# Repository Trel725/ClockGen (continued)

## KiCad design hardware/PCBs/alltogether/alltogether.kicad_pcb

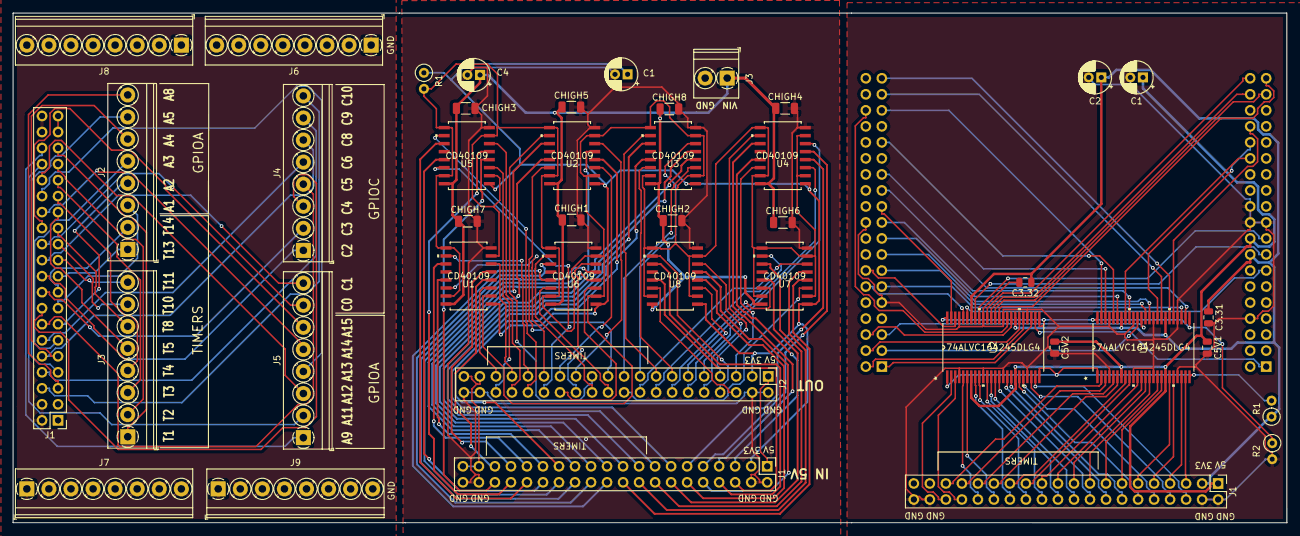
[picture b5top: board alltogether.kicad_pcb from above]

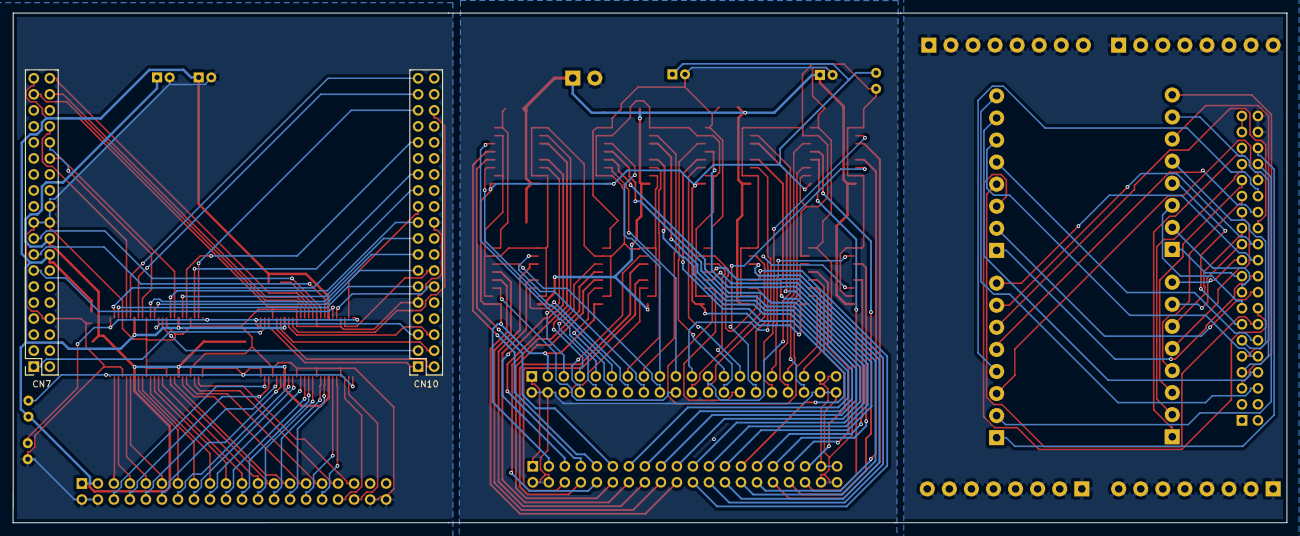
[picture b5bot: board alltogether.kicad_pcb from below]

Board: 2 copper layers, 202.0 x 80.8 mm, 44 parts (2 on the bottom side), 105 nets.

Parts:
C1, C1#2, C2, C4: CP; CP_Radial_D5.0mm_P2.00mm
C3.31, C3.32, C5V1, C5V2: C; C_0805_2012Metric
CHIGH1, CHIGH2, CHIGH3, CHIGH4, CHIGH5, CHIGH6, CHIGH7, CHIGH8: C; C_1206_3216Metric
CN7, CN10: Conn_02x19_Odd_Even; PinSocket_2x19_P2.54mm_Vertical
J1, J1#2, J1#3, J2#2: Conn_02x20_Odd_Even; PinHeader_2x20_P2.54mm_Vertical
J2, J3, J4, J5, J6, J7, J8, J9: Screw_Terminal_01x08; TerminalBlock_Phoenix_PT-1,5-8-3.5-H_1x08_P3.50mm_Horizontal
J3#2: Conn_01x02_Female; TerminalBlock_Phoenix_PT-1,5-2-3.5-H_1x02_P3.50mm_Horizontal
R1: 1K; R_Axial_DIN0207_L6.3mm_D2.5mm_P2.54mm_Vertical
R1#2, R2: 10K; R_Axial_DIN0207_L6.3mm_D2.5mm_P2.54mm_Vertical
U1, U2, U3, U4, U5, U6, U7, U8: CD40109; CD40109BNSR
U1#2, U2#2: 74ALVC164245DLG4

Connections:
+3V3: C1.1, C2.1, C3.31.1, C3.32.1, CN7.16, J1#2.3, J1#3.3, J2#2.3, R1.1, R1#2.1, U1.1, U1#2.31, U1#2.42, U2.1, U2#2.31, U2#2.42, U3.1, U4.1, U5.1, U6.1, U7.1, U8.1
+5V: C1#2.1, C5V1.1, C5V2.1, CN7.18, J1#3.1, U1#2.7, U1#2.18, U2#2.7, U2#2.18
+15V: C4.1, CHIGH1.1, CHIGH2.1, CHIGH3.1, CHIGH4.1, CHIGH5.1, CHIGH6.1, CHIGH7.1, CHIGH8.1, J3#2.1, U1.16, U2.16, U3.16, U4.16, U5.16, U6.16, U7.16, U8.16
/+5V: J1#2.1, J2#2.1
/NC: J1.37, J1.39, J1#2.37, J1#2.39, J2#2.37, J2#2.39
/PA0: CN7.28, U1#2.41
/PA0_5V: J1.27, J1#3.27, J2#2.27, J3.5, U1#2.8, U2.3
/PA0_HIGH: J1#2.27, U2.4
/PA1: CN7.30, U1#2.33
/PA1_5V: J1.15, J1#3.15, J2.3, J2#2.15, U1#2.16, U3.10
/PA1_HIGH: J1#2.15, U3.11
/PA2: CN10.35, U1#2.32
/PA2_5V: J1.13, J1#3.13, J2.4, J2#2.13, U1#2.17, U3.14
/PA2_HIGH: J1#2.13, U3.13
/PA3: CN10.37, U1#2.30
/PA3_5V: J1.11, J1#3.11, J2.5, J2#2.11, U1#2.19, U4.3
/PA3_HIGH: J1#2.11, U4.4
/PA4: CN7.32, U1#2.29
/PA4_5V: J1.9, J1#3.9, J2.6, J2#2.9, U1#2.20, U4.6
/PA4_HIGH: J1#2.9, U4.5
/PA5: CN10.11, U1#2.27
/PA5_5V: J1.7, J1#3.7, J2.7, J2#2.7, U1#2.22, U4.10
/PA5_HIGH: J1#2.7, U4.11
/PA6: CN10.13, U1#2.36
/PA6_5V: J1.19, J1#3.19, J2.1, J2#2.19, U1#2.13, U3.3
/PA6_HIGH: J1#2.19, U3.4
/PA7: CN10.15, U1#2.35
/PA7_5V: J1.17, J1#3.17, J2.2, J2#2.17, U1#2.14, U3.6
/PA7_HIGH: J1#2.17, U3.5
/PA8: CN10.23, U1#2.26
/PA8_5V: J1.5, J1#3.5, J2.8, J2#2.5, U1#2.23, U4.14
/PA8_HIGH: J1#2.5, U4.13
/PA9: CN10.21, U2#2.47
/PA9_5V: J1.36, J1#3.36, J2#2.36, J5.1, U2#2.2, U5.3
/PA9_HIGH: J1#2.36, U5.4
/PA10: CN10.33, U1#2.47
/PA10_5V: J1.35, J1#3.35, J2#2.35, J3.1, U1.3, U1#2.2
/PA10_HIGH: J1#2.35, U1.4
/PA11: CN10.14, U2#2.46
/PA11_5V: J1.34, J1#3.34, J2#2.34, J5.2, U2#2.3, U5.6
/PA11_HIGH: J1#2.34, U5.5
/PA12: CN10.12, U2#2.44
/PA12_5V: J1.32, J1#3.32, J2#2.32, J5.3, U2#2.5, U5.10
/PA12_HIGH: J1#2.32, U5.11
/PA13: CN7.13, U2#2.43
/PA13_5V: J1.30, J1#3.30, J2#2.30, J5.4, U2#2.6, U5.14
/PA13_HIGH: J1#2.30, U5.13
/PA14: CN7.15, U2#2.41
/PA14_5V: J1.28, J1#3.28, J2#2.28, J5.5, U2#2.8, U6.3
/PA14_HIGH: J1#2.28, U6.4
/PA15: CN7.17, U2#2.40
/PA15_5V: J1.26, J1#3.26, J2#2.26, J5.6, U2#2.9, U6.6
/PA15_HIGH: J1#2.26, U6.5
/PB5: CN10.29, U1#2.44
/PB5_5V: J1.31, J1#3.31, J2#2.31, J3.3, U1.10, U1#2.5
/PB5_HIGH: J1#2.31, U1.11
/PB6: CN10.17, U1#2.43
/PB6_5V: J1.29, J1#3.29, J2#2.29, J3.4, U1.14, U1#2.6
/PB6_HIGH: J1#2.29, U1.13
/PB8: CN10.3, U1#2.38
/PB8_5V: J1.23, J1#3.23, J2#2.23, J3.7, U1#2.11, U2.10
/PB8_HIGH: J1#2.23, U2.11
/PB9: CN10.5, U1#2.37
/PB9_5V: J1.21, J1#3.21, J2#2.21, J3.8, U1#2.12, U2.14
/PB9_HIGH: J1#2.21, U2.13
/PB10: CN10.25, U1#2.46
/PB10_5V: J1.33, J1#3.33, J2#2.33, J3.2, U1.6, U1#2.3
/PB10_HIGH: J1#2.33, U1.5
/PC0: CN7.38, U2#2.38
/PC0_5V: J1.24, J1#3.24, J2#2.24, J5.7, U2#2.11, U6.10
/PC0_HIGH: J1#2.24, U6.11
/PC1: CN7.36, U2#2.37
/PC1_5V: J1.22, J1#3.22, J2#2.22, J5.8, U2#2.12, U6.14
/PC1_HIGH: J1#2.22, U6.13
/PC2: CN7.35, U2#2.36
/PC2_5V: J1.20, J1#3.20, J2#2.20, J4.1, U2#2.13, U7.3
/PC2_HIGH: J1#2.20, U7.4
/PC3: CN7.37, U2#2.35
/PC3_5V: J1.18, J1#3.18, J2#2.18, J4.2, U2#2.14, U7.6
/PC3_HIGH: J1#2.18, U7.5
/PC4: CN10.34, U2#2.33
/PC4_5V: J1.16, J1#3.16, J2#2.16, J4.3, U2#2.16, U7.10
/PC4_HIGH: J1#2.16, U7.11
/PC5: CN10.6, U2#2.32
/PC5_5V: J1.14, J1#3.14, J2#2.14, J4.4, U2#2.17, U7.14
/PC5_HIGH: J1#2.14, U7.13
/PC6: CN10.4, U2#2.30
/PC6_5V: J1.12, J1#3.12, J2#2.12, J4.5, U2#2.19, U8.3
/PC6_HIGH: J1#2.12, U8.4
/PC7: CN10.19, U1#2.40
/PC7_5V: J1.25, J1#3.25, J2#2.25, J3.6, U1#2.9, U2.6
/PC7_HIGH: J1#2.25, U2.5
/PC8: CN10.2, U2#2.29
/PC8_5V: J1.10, J1#3.10, J2#2.10, J4.6, U2#2.20, U8.6
/PC8_HIGH: J1#2.10, U8.5
/PC9: CN10.1, U2#2.27
/PC9_5V: J1.8, J1#3.8, J2#2.8, J4.7, U2#2.22, U8.10
/PC9_HIGH: J1#2.8, U8.11
/PC10: CN7.1, U2#2.26
/PC10_5V: J1.6, J1#3.6, J2#2.6, J4.8, U2#2.23, U8.14
/PC10_HIGH: J1#2.6, U8.13
/PULLDOWN: R2.1, U1#2.25, U1#2.48, U2#2.25, U2#2.48
/PULLUP: R1#2.2, U1#2.1, U1#2.24, U2#2.1, U2#2.24
/PULLUP_HIGH: R1.2, U1.2, U1.7, U1.9, U1.15, U2.2, U2.7, U2.9, U2.15, U3.2, U3.7, U3.9, U3.15, U4.2, U4.7, U4.9, U4.15, U5.2, U5.7, U5.9, U5.15, U6.2, U6.7, U6.9, U6.15, U7.2, U7.7, U7.9, U7.15, U8.2, U8.7, U8.9, U8.15
GND: C1.2, C1#2.2, C2.2, C3.31.2, C3.32.2, C4.2, C5V1.2, C5V2.2, CHIGH1.2, CHIGH2.2, CHIGH3.2, CHIGH4.2, CHIGH5.2, CHIGH6.2, CHIGH7.2, CHIGH8.2, CN7.8, CN7.19, CN7.20, CN7.22, CN10.9, CN10.20, J1.2, J1.4, J1.38, J1.40, J1#2.2, J1#2.4, J1#2.38, J1#2.40, J1#3.2, J1#3.4, J1#3.38, J1#3.40, J2#2.2, J2#2.4, J2#2.38, J2#2.40, J3#2.2, J6.1, J6.2, J6.3, J6.4, J6.5, J6.6, J6.7, J6.8, J7.1, J7.2, J7.3, J7.4, J7.5, J7.6, J7.7, J7.8, J8.1, J8.2, J8.3, J8.4, J8.5, J8.6, J8.7, J8.8, J9.1, J9.2, J9.3, J9.4, J9.5, J9.6, J9.7, J9.8, R2.2, U1.8, U1#2.4, U1#2.10, U1#2.15, U1#2.21, U1#2.28, U1#2.34, U1#2.39, U1#2.45, U2.8, U2#2.4, U2#2.10, U2#2.15, U2#2.21, U2#2.28, U2#2.34, U2#2.39, U2#2.45, U3.8, U4.8, U5.8, U6.8, U7.8, U8.8

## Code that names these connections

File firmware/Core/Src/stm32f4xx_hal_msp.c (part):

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  /* USER CODE END TIM1_MspPostInit 0 */
    __HAL_RCC_GPIOA_CLK_ENABLE();
    /**TIM1 GPIO Configuration
    PA10     ------> TIM1_CH3
    */
    GPIO_InitStruct.Pin = GPIO_PIN_10;
    GPIO_InitStruct.Mode = GPIO_MODE_AF_PP;
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
    __HAL_RCC_GPIOB_CLK_ENABLE();
    /**TIM2 GPIO Configuration
    PB10     ------> TIM2_CH3
    */
    GPIO_InitStruct.Pin = GPIO_PIN_10;
    GPIO_InitStruct.Mode = GPIO_MODE_AF_PP;
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
    __HAL_RCC_GPIOB_CLK_ENABLE();
    /**TIM3 GPIO Configuration
    PB5     ------> TIM3_CH2
    */
    GPIO_InitStruct.Pin = GPIO_PIN_5;
    GPIO_InitStruct.Mode = GPIO_MODE_AF_PP;
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
    __HAL_RCC_GPIOB_CLK_ENABLE();
    /**TIM4 GPIO Configuration
    PB6     ------> TIM4_CH1
    */
    GPIO_InitStruct.Pin = GPIO_PIN_6;
    GPIO_InitStruct.Mode = GPIO_MODE_AF_PP;
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
    __HAL_RCC_GPIOA_CLK_ENABLE();
    /**TIM5 GPIO Configuration
    PA0-WKUP     ------> TIM5_CH1
    */
    GPIO_InitStruct.Pin = GPIO_PIN_0;
    GPIO_InitStruct.Mode = GPIO_MODE_AF_PP;
    GPIO_InitStruct.Pull = GPIO_PULLDOWN;
    GPIO_InitStruct.Speed = GPIO_SPEED_FREQ_LOW;
    GPIO_InitStruct.Alternate = GPIO_AF2_TIM5;
    HAL_GPIO_Init(GPIOA, &GPIO_InitStruct);
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
    __HAL_RCC_GPIOC_CLK_ENABLE();
    /**TIM8 GPIO Configuration
    PC7     ------> TIM8_CH2
    */
    GPIO_InitStruct.Pin = GPIO_PIN_7;
    GPIO_InitStruct.Mode = GPIO_MODE_AF_PP;
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
    __HAL_RCC_GPIOB_CLK_ENABLE();
    /**TIM10 GPIO Configuration
    PB8     ------> TIM10_CH1
    */
    GPIO_InitStruct.Pin = GPIO_PIN_8;
    GPIO_InitStruct.Mode = GPIO_MODE_AF_PP;
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
    __HAL_RCC_GPIOB_CLK_ENABLE();
    /**TIM11 GPIO Configuration
    PB9     ------> TIM11_CH1
    */
    GPIO_InitStruct.Pin = GPIO_PIN_9;
    GPIO_InitStruct.Mode = GPIO_MODE_AF_PP;
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
    __HAL_RCC_GPIOA_CLK_ENABLE();
    /**TIM13 GPIO Configuration
    PA6     ------> TIM13_CH1
    */
    GPIO_InitStruct.Pin = GPIO_PIN_6;
    GPIO_InitStruct.Mode = GPIO_MODE_AF_PP;
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
    __HAL_RCC_GPIOA_CLK_ENABLE();
    /**TIM14 GPIO Configuration
    PA7     ------> TIM14_CH1
    */
    GPIO_InitStruct.Pin = GPIO_PIN_7;
    GPIO_InitStruct.Mode = GPIO_MODE_AF_PP;
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
    __HAL_RCC_GPIOA_CLK_ENABLE();
    /**USART2 GPIO Configuration
    PA2     ------> USART2_TX
    PA3     ------> USART2_RX
    */
    GPIO_InitStruct.Pin = USART_TX_Pin|USART_RX_Pin;
    GPIO_InitStruct.Mode = GPIO_MODE_AF_PP;
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    __HAL_RCC_USART2_CLK_DISABLE();

    /**USART2 GPIO Configuration
    PA2     ------> USART2_TX
    PA3     ------> USART2_RX
    */
    HAL_GPIO_DeInit(GPIOA, USART_TX_Pin|USART_RX_Pin);

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
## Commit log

2021-08-19 Real initial commit
2021-08-20 Starting python part
2021-08-20 Working on it
2021-08-24 Working on host-side code
2021-08-26 Project restructured, hardware folder added
2021-08-27 Working on PCB
2021-08-29 Two PCBs are routed
2021-08-30 Screw terminal adapter added
2021-08-30 Renamed folers
2021-08-31 All PCBs concatenated to single panel
2021-09-01 Host-side software is restructured and commented
2021-09-01 Continue commenting...
2021-09-01 Documenting...
2021-09-01 Added README
2021-09-14 Added reset after execution to firmware
2021-09-26 Added methods to access frames
2021-09-27 Support low-freq timers (added prescaler)
2021-09-30 Small bugfixes
2021-11-16 Added ability to stop running generator
